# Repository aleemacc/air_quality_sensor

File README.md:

# Description
This project consists on the full development of an embedded system, with the purpose of measuring air quality.
### Included in this project:
- PCB design and schematics
- Firmware for the device
- Communication with other devices
- Integration with external systems (graphical interface)

# Characteristics
- The device will be able to measure the following:
  - Temperature
  - Humidity
  - CO2 levels
  - TVOC
  - NOx
  - LPG
  - CO
- Wireless connectivity (WiFi, BLE or LoRa)
- Modularity. Ideally you should be able to use only the sensors you need.

# Hardware
## ESP32-C6
The device is built around Seed Studio's ESP32-C6 dev-board, this simplifies the PCB design. Given its size and extensive set of features, it gives the project tons of flexibility.

## Sensors
### SCD41
Sensirion's SCD41 provides temperature, humidity and CO2 measurements with enough precision for home use. It also includes calibration for the CO2 measurements.
### SGP41
Also from Sensirion, but it measures TVOC and NOx. Temperature from the previous sensor can be used to calibrate the SGP41.
### MQ-6
Manufactured by SparkFun, this is a LPG sensor.
### MQ-7
Once again manufactured by SparkFun, this senses Carbon Monoxide.

## Display
The design features a FFC connector to add a TFT display.

## Power
When powered by the ESP's USB-C connector, the ESP board itself provides power to every component.
When a one cell battery pack is used (ie. 18650 or 18300 Li-ion), components powered by 3V3 are still managed by the ESP. However, sensors requiring 5V are powered through a Boost Converter that transforms the batteries voltage to a steady 5V.

## Interfaces
The sensor SCD41 and SGP41 communicate over I2C, both MQ-x sensors use an analog signal and the display will be set up to use 4-wire SPI.

# PCB
The current version of the project features a 2 layer PCB, with the bottom one being a ground plane.
The large space in the middle is there to give space for a 18650 or 18300 battery (depending on which sensors are installed). It also serves to distance the SCD41 sensor from heat sources, such as the MCU or the boost converter.
The SCD41 sensor is excluded from the ground plane and placed within an isolation island, for better accuracy in the temperature measurements

# Firmware
This device is intended to work both with home assistant and independently.
For now only yaml code has been added for testing in home assistant with limited functionality.

# Images

  <br>
This shows the first working prototype on a breadboard, only with the SCD41 and the SGP41 sensors.

# Documentation
All the documentation used for the design of the PCB can be found at `./hardware/kicad/docs/`

# License
This project is licensed under multiple licenses:

- Firmware: Apache License 2.0
- Hardware: CERN Open Hardware Licence v2 - Permissive (OHL-P)

See the LICENSE files in each directory for details.

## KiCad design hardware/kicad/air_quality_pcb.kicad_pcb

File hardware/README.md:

The hardware in this project is licensed under the **CERN-OHL-P v2.0** license.

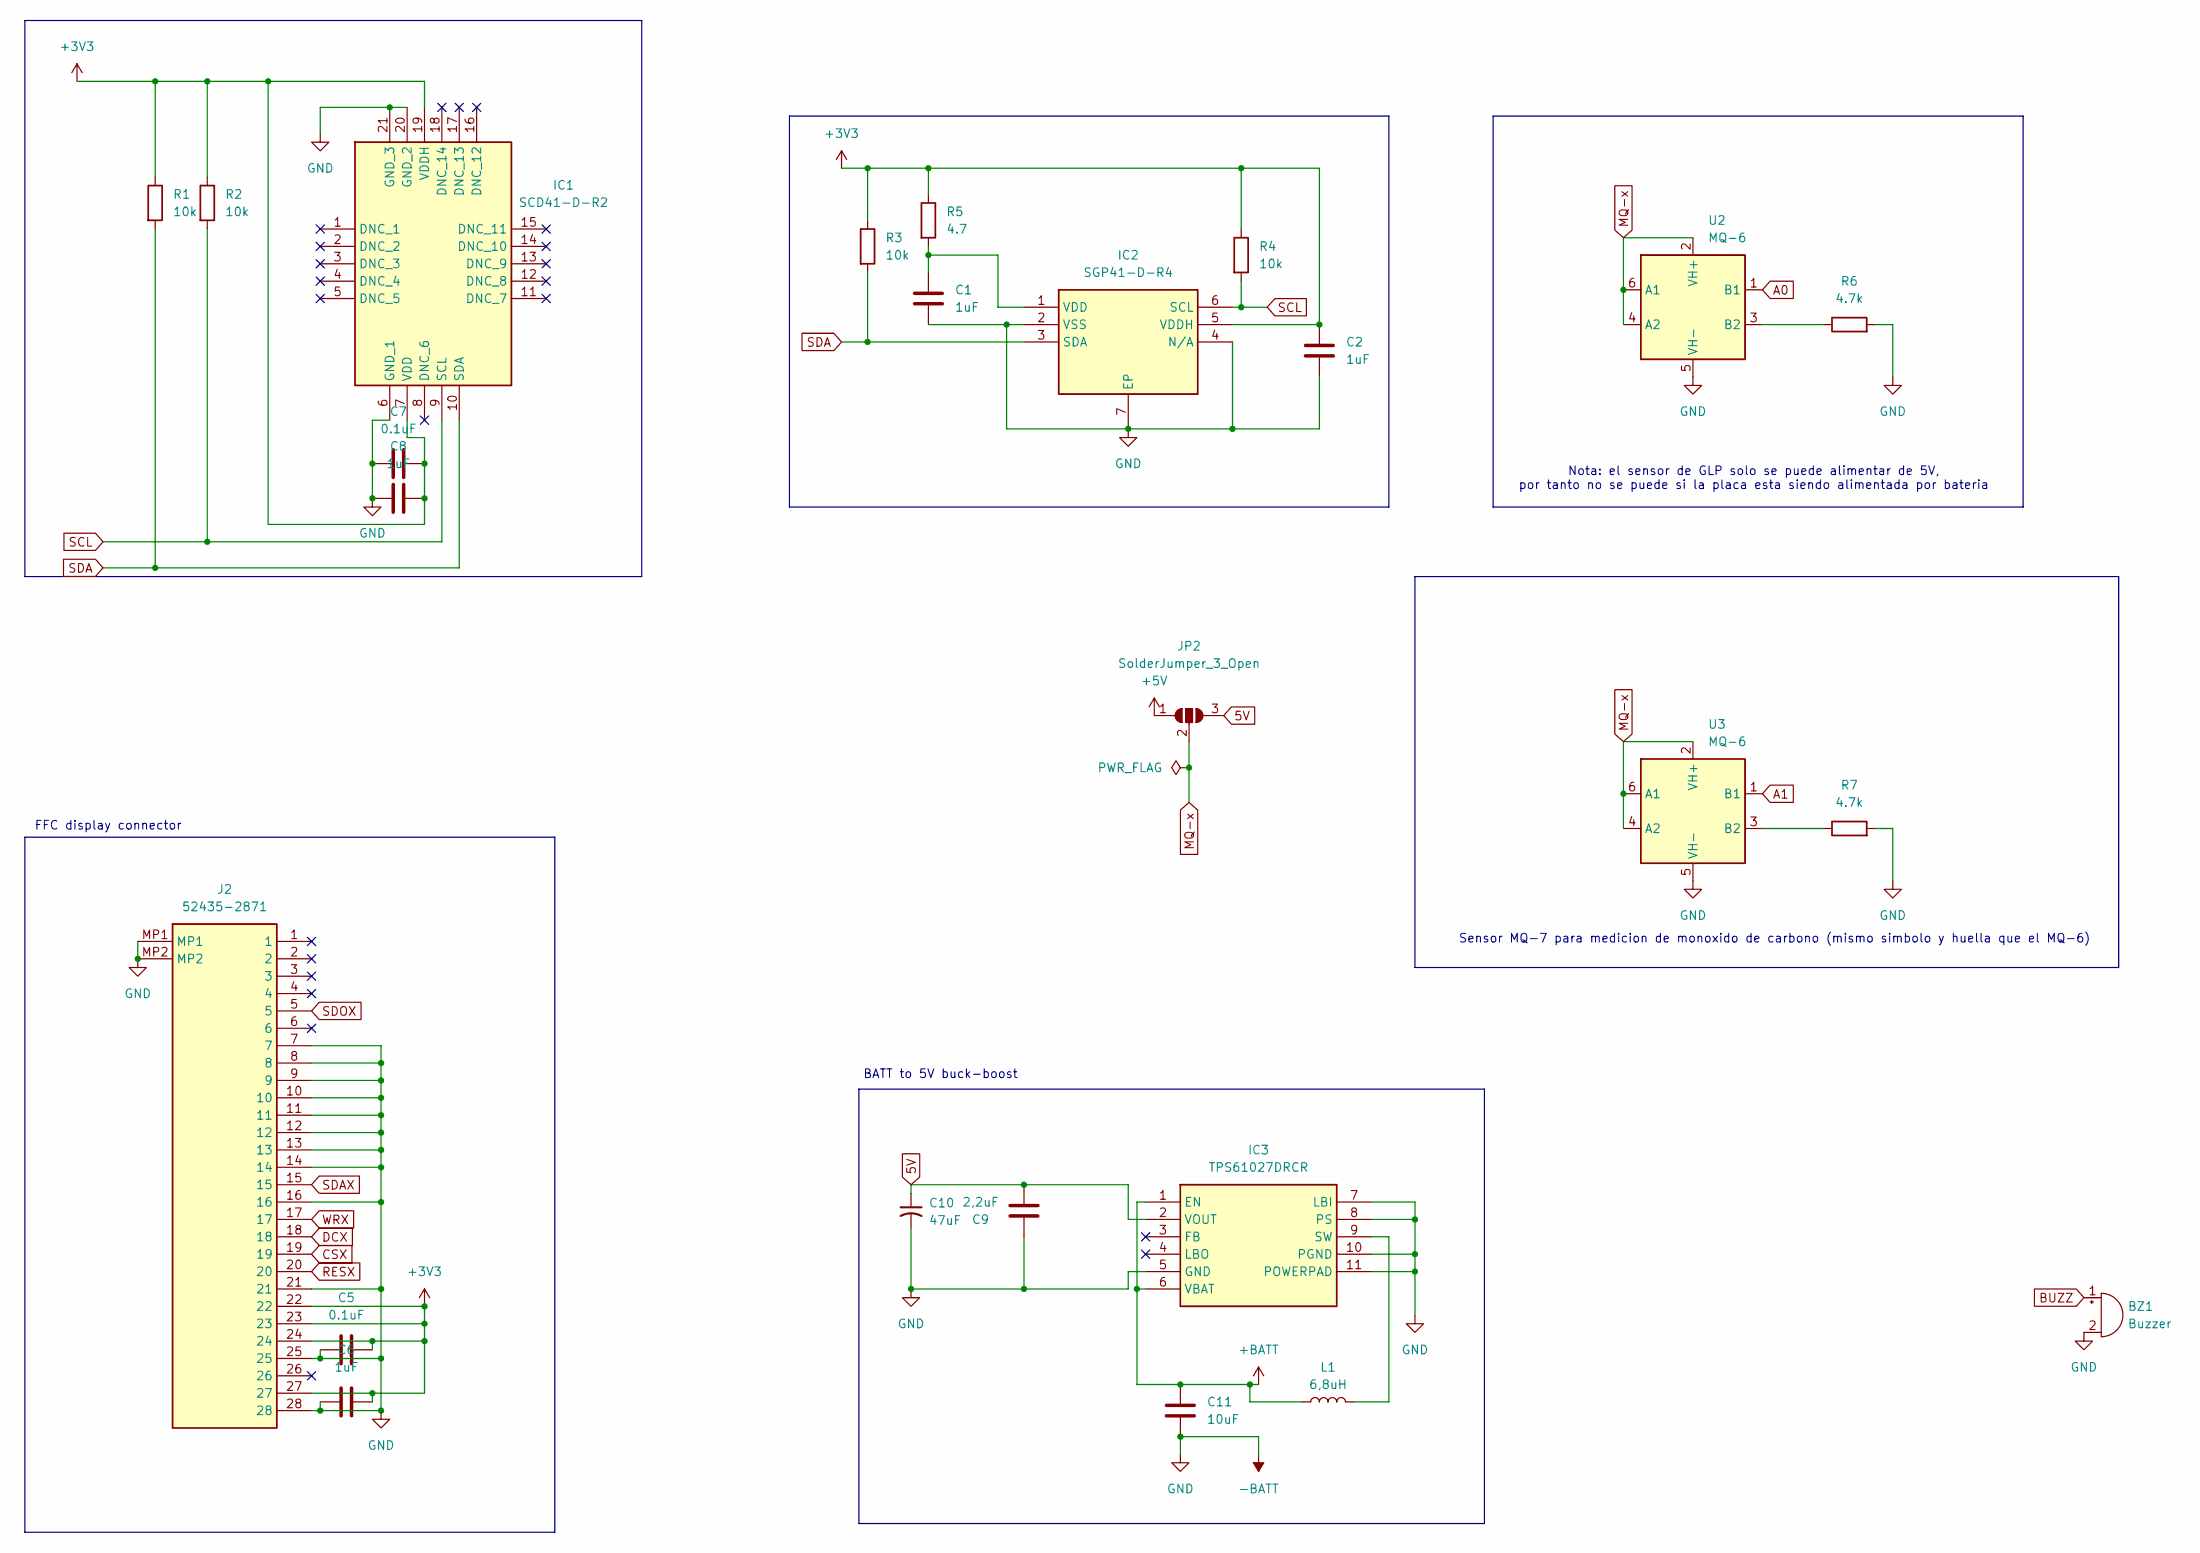
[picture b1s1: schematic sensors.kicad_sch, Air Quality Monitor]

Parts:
BZ1: Buzzer; Buzzer_12x9.5RM7.6
C1, C2, C6, C8: 1uF; C_1206_3216Metric
C5, C7: 0.1uF; C_1206_3216Metric
C9: 2,2uF; C_1206_3216Metric
C10: 47uF; CAPPM3216X180N
C11: 10uF; C_1206_3216Metric
IC1: SCD41-D-R2; SCD41DR2; Manufacturer_Part_Number SCD41-D-R2; Mouser Part Number 403-SCD41-D-R2
IC2: SGP41-D-R4; SGP41; Manufacturer_Part_Number SGP41-D-R4; Mouser Part Number 403-SGP41-D-R4
IC3: TPS61027DRCR; TPS74901DRCR; Manufacturer_Part_Number TPS61027DRCR; Mouser Part Number 595-TPS61027DRCR
J2: 52435-2871; display_connector; Manufacturer_Part_Number 52435-2871; Mouser Part Number 538-52435-2871
JP2: SolderJumper_3_Open; SolderJumper-3_P1.3mm_Open_RoundedPad1.0x1.5mm_NumberLabels
L1: 6,8uH; INDPM6363X300N
R1, R2, R3, R4: 10k; R_1206_3216Metric
R5: 4.7; R_1206_3216Metric
R6, R7: 4.7k; R_1206_3216Metric
U2, U3: MQ-6

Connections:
5V: C9.1, C10.1, IC3.2 (VOUT), JP2.3 (B)
+3V3: C2.1, C5.1, C6.1, C7.2, C8.2, IC1.7 (VDD), IC1.19 (VDDH), IC2.5 (VDDH), J2.22, J2.23, J2.24, J2.27, R1.1, R2.1, R3.1, R4.1, R5.1; also elsewhere on the board
+5V: JP2.1 (A); also elsewhere on the board
+BATT: C11.2, IC3.1 (EN), IC3.6 (VBAT), L1.1; also elsewhere on the board
-BATT: BZ1.2 (-), C1.2, C2.2, C5.2, C6.2, C7.1, C8.1, C9.2, C10.2, C11.1, IC1.6 (GND_1), IC1.20 (GND_2), IC1.21 (GND_3), IC2.2 (VSS), IC2.4 (N/A), IC2.7 (EP), IC3.5 (GND), IC3.7 (LBI), IC3.8 (PS), IC3.10 (PGND), IC3.11 (POWERPAD), J2.7, J2.8, J2.9, J2.10, J2.11, J2.12, J2.13, J2.14, J2.16, J2.21, J2.25, J2.28, J2.MP1, J2.MP2, R6.2, R7.2, U2.5 (VH-), U3.5 (VH-); also elsewhere on the board
A0: U2.1 (B1); also elsewhere on the board
A1: U3.1 (B1); also elsewhere on the board
BUZZ: BZ1.1 (+); also elsewhere on the board
CSX: J2.19; also elsewhere on the board
DCX: J2.18; also elsewhere on the board
MQ-x: JP2.2 (C), U2.2 (VH+), U2.4 (A2), U2.6 (A1), U3.2 (VH+), U3.4 (A2), U3.6 (A1)
unnamed: C1.1, IC2.1 (VDD), R5.2
unnamed: IC3.9 (SW), L1.2
unnamed: R6.1, U2.3 (B2)
unnamed: R7.1, U3.3 (B2)
RESX: J2.20; also elsewhere on the board
SCL: IC1.9 (SCL), IC2.6 (SCL), R2.2, R4.2; also elsewhere on the board
SDA: IC1.10 (SDA), IC2.3 (SDA), R1.2, R3.2; also elsewhere on the board
SDAX: J2.15; also elsewhere on the board
SDOX: J2.5; also elsewhere on the board
WRX: J2.17; also elsewhere on the board

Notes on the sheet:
Nota: el sensor de GLP solo se puede alimentar de 5V, por tanto no se puede si la placa esta siendo alimentada por bateria
BATT to 5V buck-boost
Sensor MQ-7 para medicion de monoxido de carbono (mismo simbolo y huella que el MQ-6)
FFC display connector

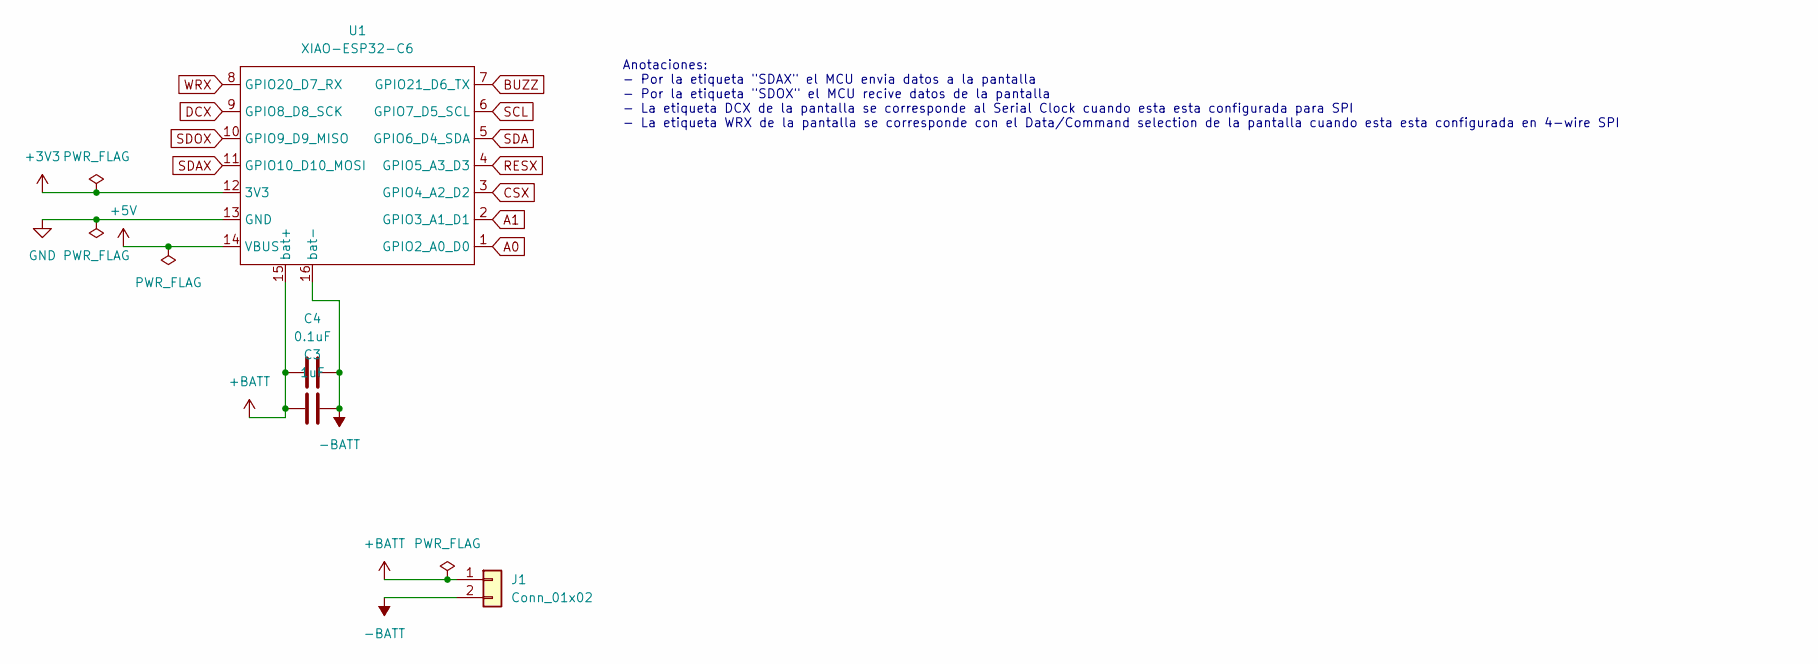
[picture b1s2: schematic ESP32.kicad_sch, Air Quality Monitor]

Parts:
C3: 1uF; C_1206_3216Metric
C4: 0.1uF; C_1206_3216Metric
J1: Conn_01x02; BATT_connector
U1: XIAO-ESP32-C6; XIAO-ESP32-C6-SMD

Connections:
+3V3: U1.12 (3V3); also elsewhere on the board
+5V: U1.14 (VBUS); also elsewhere on the board
+BATT: C3.1, C4.1, J1.1, U1.15 (bat+); also elsewhere on the board
-BATT: C3.2, C4.2, J1.2, U1.13 (GND), U1.16 (bat-); also elsewhere on the board
A0: U1.1 (GPIO2_A0_D0); also elsewhere on the board
A1: U1.2 (GPIO3_A1_D1); also elsewhere on the board
BUZZ: U1.7 (GPIO21_D6_TX); also elsewhere on the board
CSX: U1.3 (GPIO4_A2_D2); also elsewhere on the board
DCX: U1.9 (GPIO8_D8_SCK); also elsewhere on the board
RESX: U1.4 (GPIO5_A3_D3); also elsewhere on the board
SCL: U1.6 (GPIO7_D5_SCL); also elsewhere on the board
SDA: U1.5 (GPIO6_D4_SDA); also elsewhere on the board
SDAX: U1.11 (GPIO10_D10_MOSI); also elsewhere on the board
SDOX: U1.10 (GPIO9_D9_MISO); also elsewhere on the board
WRX: U1.8 (GPIO20_D7_RX); also elsewhere on the board

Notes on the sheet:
Anotaciones: - Por la etiqueta "SDAX" el MCU envia datos a la pantalla - Por la etiqueta "SDOX" el MCU recive datos de la pantalla - La etiqueta DCX de la pantalla se corresponde al Serial Clock cuando esta esta configurada para SPI - La etiqueta WRX de la pantalla se corresponde con el Data/Comman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

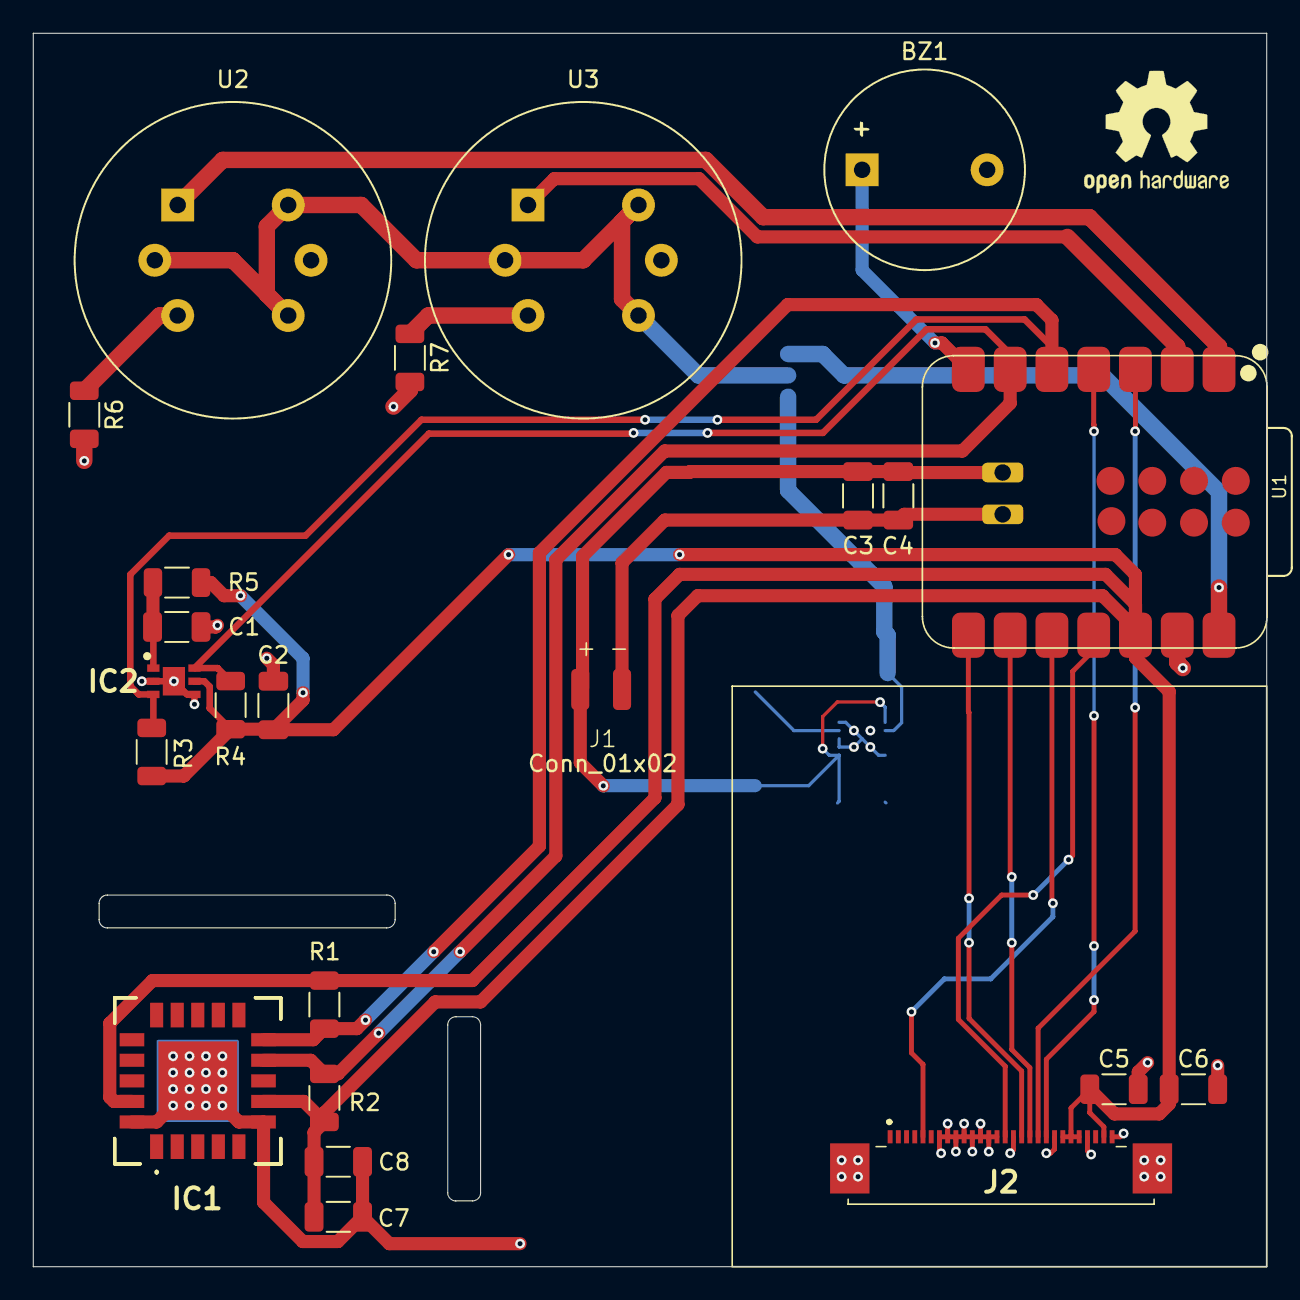
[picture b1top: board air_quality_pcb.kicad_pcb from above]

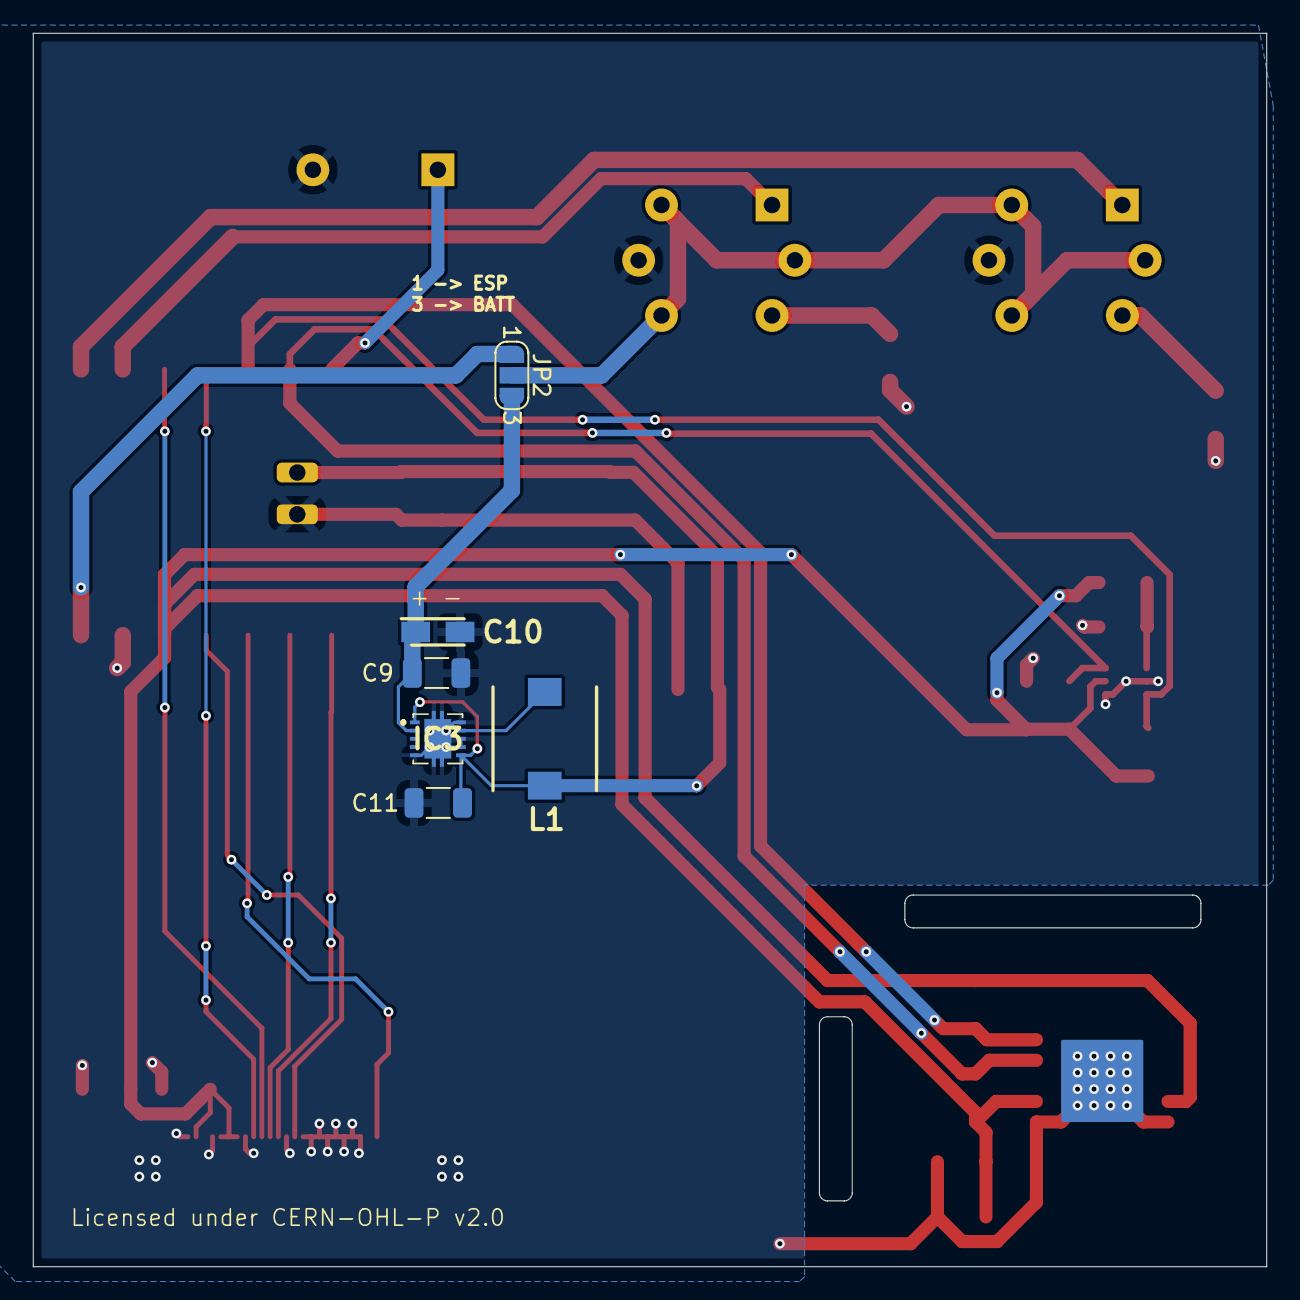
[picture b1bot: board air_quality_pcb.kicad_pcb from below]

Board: 2 copper layers, 75.0 x 75.0 mm, 29 parts (6 on the bottom side), 21 nets.

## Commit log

2026-04-14 add readme
2026-04-15 added sensors and display example
2026-04-15 added mq7 sensor and display connector
2026-04-15 finished routing and added more decoupling caps
2026-04-19 added buck boost for 5v battery powered
2026-04-20 added buzzer
2026-04-28 fixed buzzer and MQ-x sensors placement
2026-04-28 gitignore added
2026-04-28 fixed silkscreen
2026-04-28 improved README
2026-05-10 refactor: changed hardware folder name
2026-05-10 chore: updated README for the new folder naming
2026-05-10 chore: added licensing
2026-05-11 feat: added yaml code for hommeassistant
2026-05-11 chore: added images and short firmware description to the readme
2026-05-11 chore: resized image on readme

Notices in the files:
hardware/README.md:
License: CERN-OHL-P v2.0
hardware/kicad/ESP32.kicad_sch:
Licensed under CERN-OHL-P-2.0
hardware/kicad/air_quality_pcb.kicad_pcb:
Licensed under CERN-OHL-P v2.0
